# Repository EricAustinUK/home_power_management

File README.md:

# Home Power Management

A bespoke home power management system built on a Raspberry Pi Zero W, optimised by edge AI and written in Rust.
Predicts solar generation with an on-device ML model, then calculates and schedules battery and EV charging around a cheap energy tariff window via Home Assistant. 

## How it works

- **Solar prediction (`ml/`)**: a compact regression model trained on historical weather and solar pv generation data predicts the next 24 hours of solar output. Inference runs locally on the Pi Zero W (ARMv6, 512 MB RAM).
- **Weather input(`software/home_manager/weather_data.rs`)**: hourly forecasts from the OpenMeteo API feed the model.
- **Battery scheduling**: during tariff windows, the expected house load is compared against predicted solar, the battery is configured to charge to cover any shortfall, then reset to its baseline when the tariff ends.
- **EV conditional charging**: reads an EV's battery level, home location, and plug state from Home Assistant to control an IoT enabled charger, switching it off once the target charge (currently 95%) is reached.
- **Control panel (`control_panel.rs`)**: a physical panel (currently on a breadboard) with three "appliance" toggle switches (though only one of these is currently configured, being the one representing the home being inhabited) that feed into the estimate for home energy consumption. Shows the state for each these appliances with an LED. 

## Optimization for ARM

The model and inference path were developed with the Pi Zero W's hardware limitations in mind.

| Metric | Value |
|---|---|
| Model size on disk | 282B |
| Model data size on disk | 99KB |
| Inference latency (Pi Zero W) | 1.51ms |
| RAM footprint | 3664KB |

## Hardware

- Raspberry Pi Zero W
- Custom control panel housing 3 push switches with pull-ups, status LEDs
- Home Assistant instance with battery, EV, and charger integrations

## Setup

1. Clone and copy `.env.example` to `.env`, filling in:
   - `HASS_IP`, `HASS_PORT`, `HASS_TOKEN` (long-lived access token obtained in Home Assistant developer settings)
   - `BATTERY_NAME`, `EV_NAME`, `EV_CHARGER_NAME` - entity prefixes as they appear in Home Assistant. Current implementation is for an Ecoflow battery, a BYD EV and a VOLDT charger connected to SmartLife; using [hass-byd-vehicle](https://github.com/jkaberg/hass-byd-vehicle), [hassio-ecoflow-cloud](https://github.com/tolwi/hassio-ecoflow-cloud), HomeAssistant's official Tuya SmartLife integration
   - `WEATHER_API_URL`, `PANEL_LATITUDE`, `PANEL_LONGITUDE` - for the weather forecast and history. Currently only OpenMeteo is supported
   - `MODEL_FILENAME`, `MODEL_DATA_FILENAME` - trained model binary if training off the target is preferred (see `ml/`)
2. Cross-compile for the Pi Zero W:
   ```bash
   cd software
   cargo build --target arm-unknown-linux-musleabihf --release
   ```
   (requires the `arm-linux-gnueabihf-gcc` linker)
3. Deploy and run (uses `PI_USER` and `PI_HOST` from `.env`):
   ```bash
   set -a && source ../.env && set +a
   scp target/arm-unknown-linux-musleabihf/release/home_assist $PI_USER@$PI_HOST:~/
   ssh $PI_USER@$PI_HOST "chmod +x ~/home_assist && ~/home_assist"
   ```
   (also available as the "deploy to pi" / "run on pi" tasks in `.vscode/tasks.json`)

## License

MIT, see [LICENSE](LICENSE)

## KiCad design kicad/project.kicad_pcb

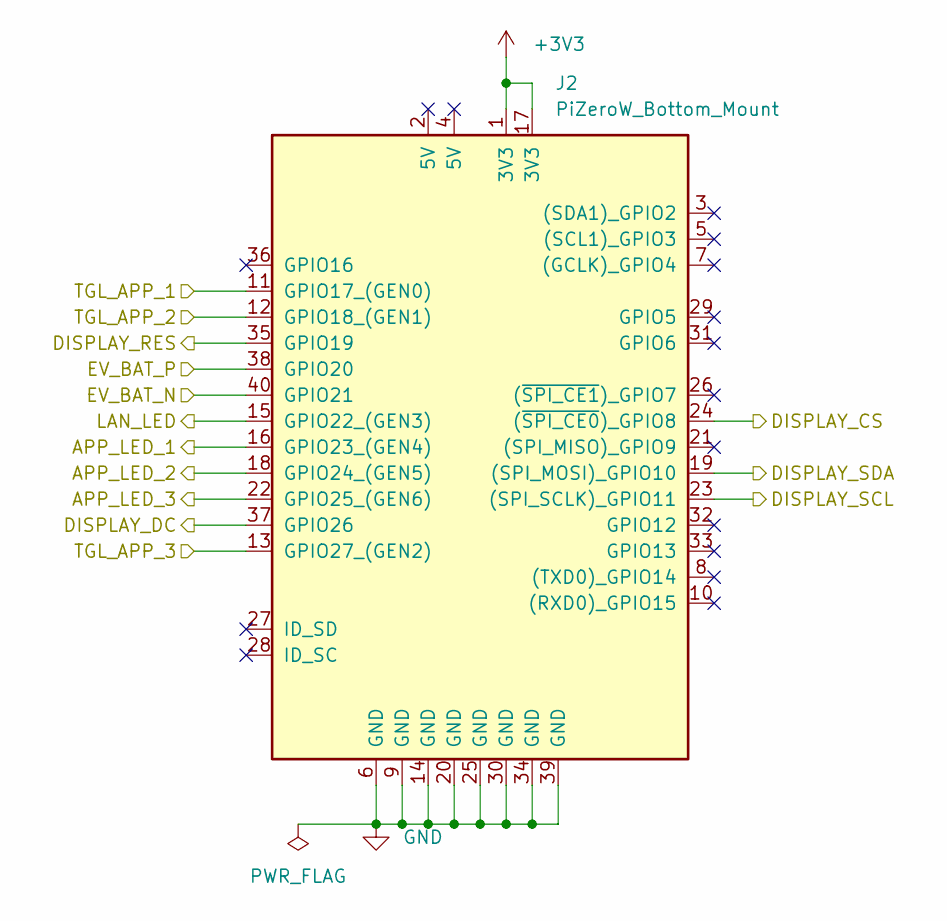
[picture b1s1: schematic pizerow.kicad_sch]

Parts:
J2: PiZeroW_Bottom_Mount; PinHeader_2x20_P2.54mm_Vertical

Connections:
+3V3: J2.1 (3V3), J2.17 (3V3); also elsewhere on the board
/Control_Panel/EV_BAT_N: J2.40 (GPIO21); also elsewhere on the board
/Control_Panel/EV_BAT_P: J2.38 (GPIO20); also elsewhere on the board
/Control_Panel/TGL_APP_1: J2.11 (GPIO17_(GEN0)); also elsewhere on the board
/Control_Panel/TGL_APP_2: J2.12 (GPIO18_(GEN1)); also elsewhere on the board
/Control_Panel/TGL_APP_3: J2.13 (GPIO27_(GEN2)); also elsewhere on the board
/LCD_Display/LCD_CS: J2.24 ((~SPI_CE0)_GPIO8); also elsewhere on the board
/LCD_Display/LCD_DC: J2.37 (GPIO26); also elsewhere on the board
/LCD_Display/LCD_RES: J2.35 (GPIO19); also elsewhere on the board
/LCD_Display/LCD_SCL: J2.23 ((SPI_SCLK)_GPIO11); also elsewhere on the board
/LCD_Display/LCD_SDA: J2.19 ((SPI_MOSI)_GPIO10); also elsewhere on the board
/LED_Panel/APP_LED_1: J2.16 (GPIO23_(GEN4)); also elsewhere on the board
/LED_Panel/APP_LED_2: J2.18 (GPIO24_(GEN5)); also elsewhere on the board
/LED_Panel/APP_LED_3: J2.22 (GPIO25_(GEN6)); also elsewhere on the board
/LED_Panel/LAN_LED: J2.15 (GPIO22_(GEN3)); also elsewhere on the board
GND: J2.6 (GND), J2.9 (GND), J2.14 (GND), J2.20 (GND), J2.25 (GND), J2.30 (GND), J2.34 (GND), J2.39 (GND); also elsewhere on the board

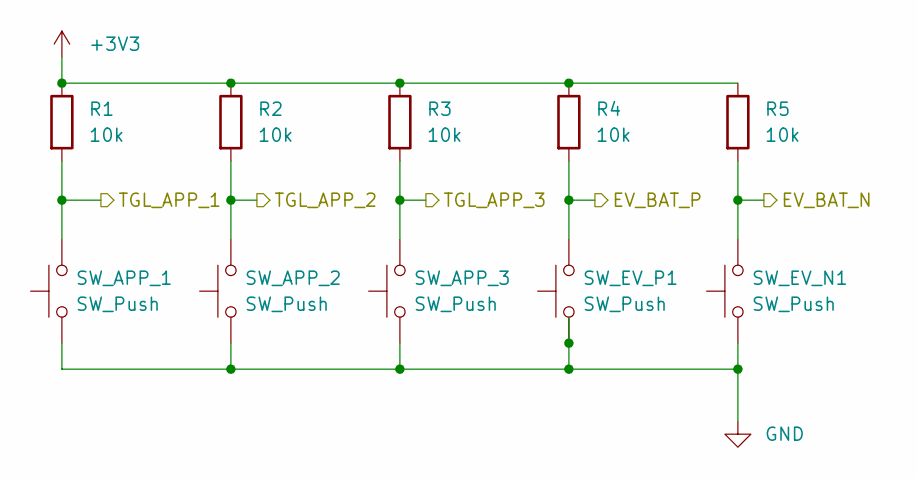
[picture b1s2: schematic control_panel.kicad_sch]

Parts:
R1, R2, R3, R4, R5: 10k; R_0603_1608Metric
SW_APP_1, SW_APP_2, SW_APP_3: SW_Push; SW_SPST_PTS810
SW_EV_N1: SW_Push; SW_SPST_PTS810
SW_EV_P1: SW_Push; SW_SPST_PTS810

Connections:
+3V3: R1.1, R2.1, R3.1, R4.1, R5.1; also elsewhere on the board
/Control_Panel/EV_BAT_N: R5.2, SW_EV_N1.2; also elsewhere on the board
/Control_Panel/EV_BAT_P: R4.2, SW_EV_P1.2; also elsewhere on the board
/Control_Panel/TGL_APP_1: R1.2, SW_APP_1.2; also elsewhere on the board
/Control_Panel/TGL_APP_2: R2.2, SW_APP_2.2; also elsewhere on the board
/Control_Panel/TGL_APP_3: R3.2, SW_APP_3.2; also elsewhere on the board
GND: SW_APP_1.1, SW_APP_2.1, SW_APP_3.1, SW_EV_N1.1, SW_EV_P1.1; also elsewhere on the board

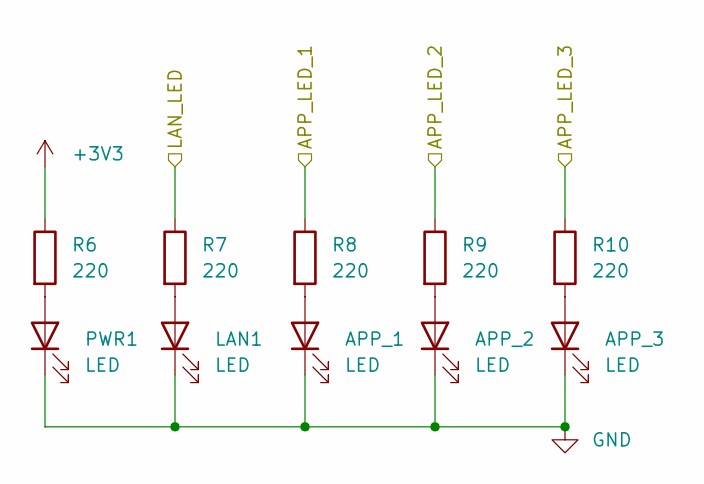
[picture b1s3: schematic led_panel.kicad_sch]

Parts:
APP_1, APP_2, APP_3: LED; LED_0805_2012Metric
LAN1: LED; LED_0805_2012Metric
PWR1: LED; LED_0805_2012Metric
R6, R7, R8, R9, R10: 220; R_0603_1608Metric

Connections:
+3V3: R6.1; also elsewhere on the board
/LED_Panel/APP_LED_1: R8.1; also elsewhere on the board
/LED_Panel/APP_LED_2: R9.1; also elsewhere on the board
/LED_Panel/APP_LED_3: R10.1; also elsewhere on the board
/LED_Panel/LAN_LED: R7.1; also elsewhere on the board
GND: APP_1.1 (K), APP_2.1 (K), APP_3.1 (K), LAN1.1 (K), PWR1.1 (K); also elsewhere on the board
unnamed: APP_1.2 (A), R8.2
unnamed: APP_2.2 (A), R9.2
unnamed: APP_3.2 (A), R10.2
unnamed: LAN1.2 (A), R7.2
unnamed: PWR1.2 (A), R6.2

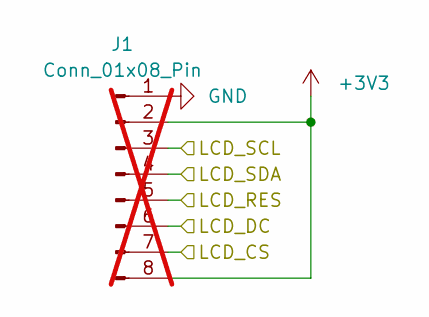
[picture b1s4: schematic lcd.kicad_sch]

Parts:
J1: Conn_01x08_Pin; PinHeader_1x08_P2.54mm_Vertical; not fitted

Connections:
+3V3: J1.2, J1.8; also elsewhere on the board
/LCD_Display/LCD_CS: J1.7; also elsewhere on the board
/LCD_Display/LCD_DC: J1.6; also elsewhere on the board
/LCD_Display/LCD_RES: J1.5; also elsewhere on the board
/LCD_Display/LCD_SCL: J1.3; also elsewhere on the board
/LCD_Display/LCD_SDA: J1.4; also elsewhere on the board
GND: J1.1; also elsewhere on the board

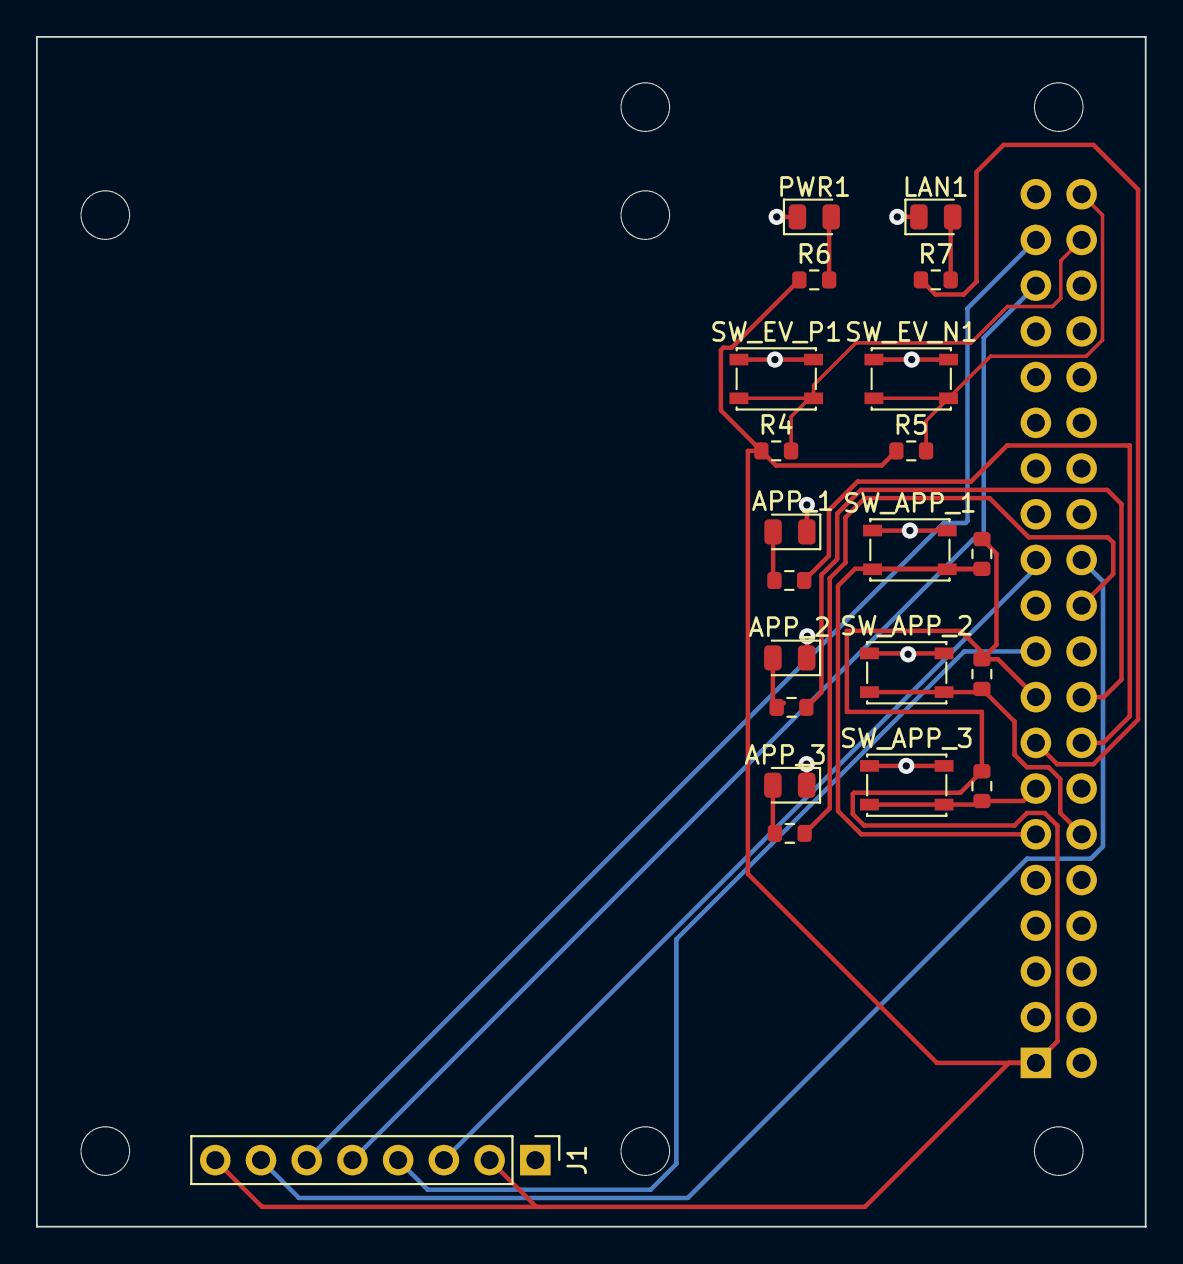
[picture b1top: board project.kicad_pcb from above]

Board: 2 copper layers, 61.6 x 66.1 mm, 29 parts (1 on the bottom side), 21 nets.

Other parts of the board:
H1, H2, H3, H4/7, H5, H6, H8: MountingHole_2.7mm_M2.5
